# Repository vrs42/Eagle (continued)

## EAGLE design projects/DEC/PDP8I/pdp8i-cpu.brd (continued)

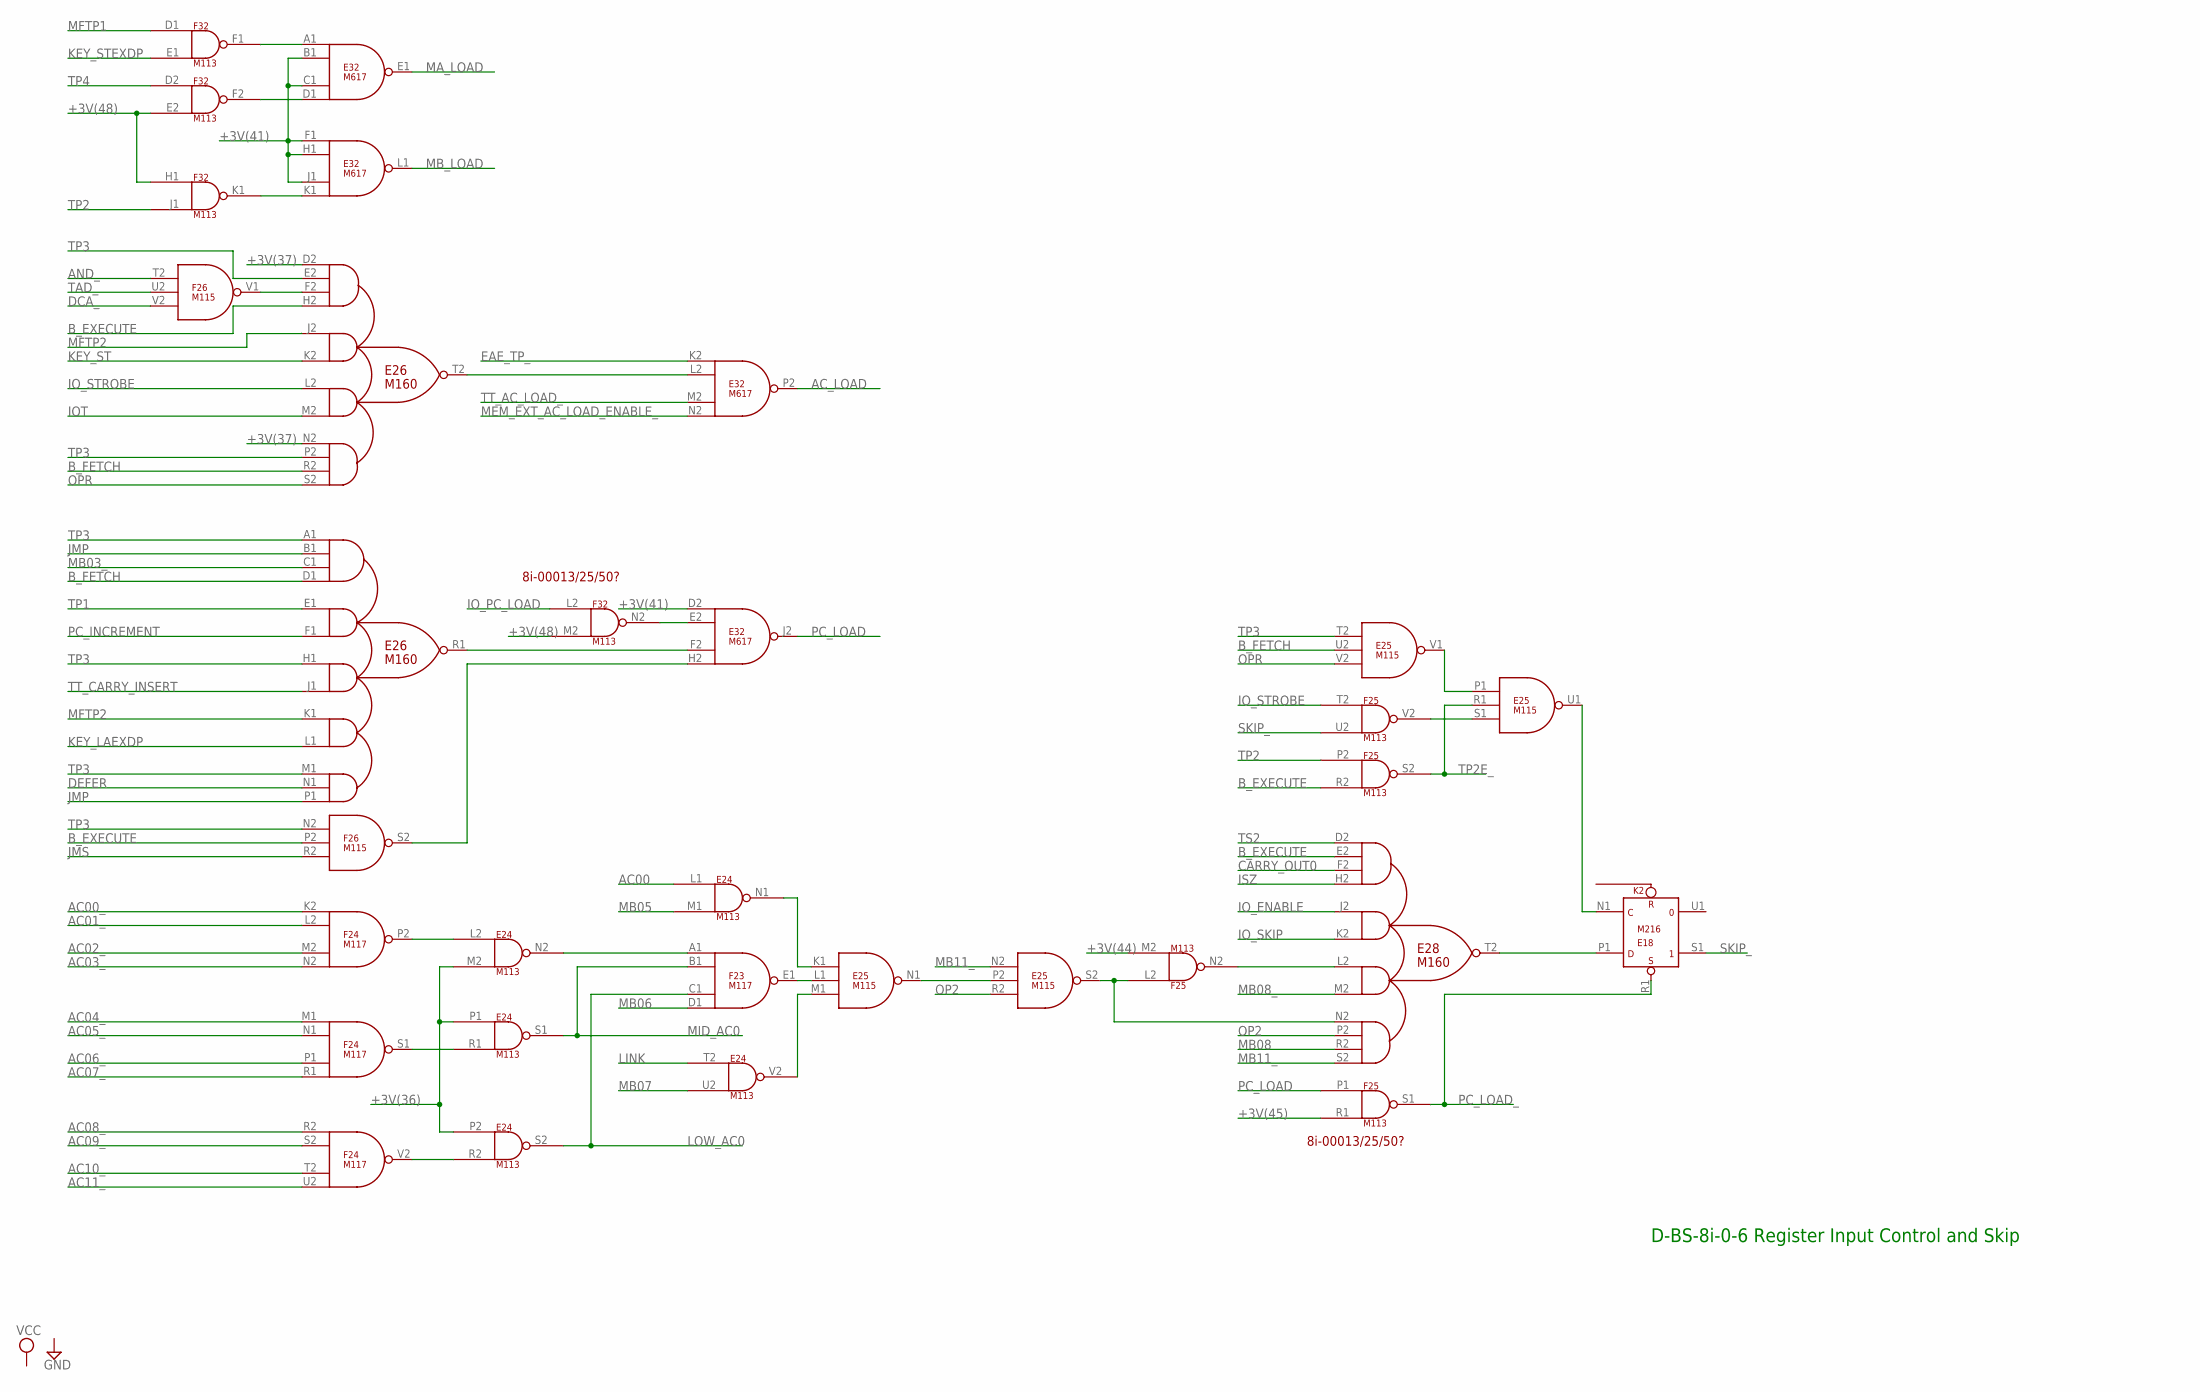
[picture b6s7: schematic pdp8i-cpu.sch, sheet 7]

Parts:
E18: M216; H807
E24: M113; H807
E25: M115; H807
E26, E28: M160; H807
E32: M617; H807
F23, F24: M117; H807
F25, F32: M113; H807
F26: M115; H807

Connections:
+3V(36): E24.M2 (IN2), E24.P1 (IN1), E24.P2 (IN1); also elsewhere on the board
+3V(37): E26.D2 (IN1A), E26.N2 (IN4A); also elsewhere on the board
+3V(41): E32.B1 (IN2), E32.C1 (IN3), E32.D2 (IN1), E32.F1 (IN1), E32.H1 (IN2), E32.J1 (IN3); also elsewhere on the board
+3V(44): F25.M2 (IN2); also elsewhere on the board
+3V(45): F25.R1 (IN2); also elsewhere on the board
+3V(48): F32.E2 (IN2), F32.H1 (IN1), F32.M2 (IN2); also elsewhere on the board
AC00: E24.L1 (IN1); also elsewhere on the board
AC00_: F24.K2 (IN1); also elsewhere on the board
AC01_: F24.L2 (IN2); also elsewhere on the board
AC02_: F24.M2 (IN3); also elsewhere on the board
AC03_: F24.N2 (IN4); also elsewhere on the board
AC04_: F24.M1 (IN1); also elsewhere on the board
AC05_: F24.N1 (IN2); also elsewhere on the board
AC06_: F24.P1 (IN3); also elsewhere on the board
AC07_: F24.R1 (IN4); also elsewhere on the board
AC08_: F24.R2 (IN1); also elsewhere on the board
AC09_: F24.S2 (IN2); also elsewhere on the board
AC10_: F24.T2 (IN3); also elsewhere on the board
AC11_: F24.U2 (IN4); also elsewhere on the board
AC_LOAD: E32.P2 (OUT); also elsewhere on the board
AND_: F26.T2 (IN1); also elsewhere on the board
B_EXECUTE: E26.H2 (IN1D), E28.E2 (IN1B), F25.R2 (IN2), F26.P2 (IN2); also elsewhere on the board
B_FETCH: E25.U2 (IN2), E26.D1 (IN1D), E26.R2 (IN4C); also elsewhere on the board
CARRY_OUT0: E28.F2 (IN1C); also elsewhere on the board
DCA_: F26.V2 (IN3); also elsewhere on the board
DEFER: E26.N1 (IN5B); also elsewhere on the board
EAE_TP_: E32.K2 (IN1); also elsewhere on the board
GND: E18.C2 (GND), E18.T1 (GND), E24.C2 (GND), E24.T1 (GND), E25.C2 (GND), E25.T1 (GND), E26.C2 (GND), E26.T1 (GND), E28.C2 (GND), E28.T1 (GND), E32.C2 (GND), E32.T1 (GND), F23.C2 (GND), F23.T1 (GND), F24.C2 (GND), F24.T1 (GND), F25.C2 (GND), F25.T1 (GND), F26.C2 (GND), F26.T1 (GND), F32.C2 (GND), F32.T1 (GND); also elsewhere on the board
IOT: E26.M2 (IN3B); also elsewhere on the board
IO_ENABLE: E28.J2 (IN2A); also elsewhere on the board
IO_PC_LOAD: F32.L2 (IN1); also elsewhere on the board
IO_SKIP: E28.K2 (IN2B); also elsewhere on the board
IO_STROBE: E26.L2 (IN3A), F25.T2 (IN1); also elsewhere on the board
ISZ: E28.H2 (IN1D); also elsewhere on the board
JMP: E26.B1 (IN1B), E26.P1 (IN5C); also elsewhere on the board
JMS: F26.R2 (IN3); also elsewhere on the board
KEY_LAEXDP: E26.L1 (IN4B); also elsewhere on the board
KEY_ST: E26.K2 (IN2B); also elsewhere on the board
KEY_STEXDP: F32.E1 (IN2); also elsewhere on the board
LINK: E24.T2 (IN1); also elsewhere on the board
LOW_AC0: E24.S2 (OUT), F23.C1 (IN3); also elsewhere on the board
MA_LOAD: E32.E1 (OUT); also elsewhere on the board
MB03_: E26.C1 (IN1C); also elsewhere on the board
MB05: E24.M1 (IN2); also elsewhere on the board
MB06: F23.D1 (IN4); also elsewhere on the board
MB07: E24.U2 (IN2); also elsewhere on the board
MB08: E28.R2 (IN4C); also elsewhere on the board
MB08_: E28.M2 (IN3B); also elsewhere on the board
MB11_: E25.N2 (IN1), E28.S2 (IN4D); also elsewhere on the board
MB_LOAD: E32.L1 (OUT); also elsewhere on the board
MEM_EXT_AC_LOAD_ENABLE_: E32.N2 (IN4); also elsewhere on the board
MFTP1: F32.D1 (IN1); also elsewhere on the board
MFTP2: E26.J2 (IN2A), E26.K1 (IN4A); also elsewhere on the board
MID_AC0: E24.S1 (OUT), F23.B1 (IN2); also elsewhere on the board
unnamed: E32.E2 (IN2), F32.N2 (OUT)
unnamed: E26.F2 (IN1C), F26.V1 (OUT)
unnamed: E26.T2 (OUT), E32.L2 (IN2)
unnamed: E26.R1 (OUT), E32.F2 (IN3)
unnamed: E32.H2 (IN4), F26.S2 (OUT)
unnamed: E24.R2 (IN2), F24.V2 (OUT)
unnamed: E24.R1 (IN2), F24.S1 (OUT)
unnamed: E24.L2 (IN1), F24.P2 (OUT)
unnamed: E25.L1 (IN2), F23.E1 (OUT)
unnamed: E24.V2 (OUT), E25.M1 (IN3)
unnamed: E24.N2 (OUT), F23.A1 (IN1)
unnamed: E24.N1 (OUT), E25.K1 (IN1)
unnamed: E25.N1 (OUT), E25.P2 (IN2)
unnamed: E28.L2 (IN3A), F25.N2 (OUT)
unnamed: E25.S2 (OUT), E28.N2 (IN4A), F25.L2 (IN1)
unnamed: E18.P1 (D), E28.T2 (OUT)
unnamed: E32.D1 (IN4), F32.F2 (OUT)
unnamed: E32.A1 (IN1), F32.F1 (OUT)
unnamed: E18.N1 (C), E25.U1 (OUT)
unnamed: E32.K1 (IN4), F32.K1 (OUT)
unnamed: E25.P1 (IN1), E25.V1 (OUT)
unnamed: E25.S1 (IN3), F25.V2 (OUT)
OP2: E25.R2 (IN3), E28.P2 (IN4B); also elsewhere on the board
OPR: E25.V2 (IN3), E26.S2 (IN4D); also elsewhere on the board
PC_INCREMENT: E26.F1 (IN2B); also elsewhere on the board
PC_LOAD: E32.J2 (OUT), F25.P1 (IN1); also elsewhere on the board
PC_LOAD_: E18.R1 (S), F25.S1 (OUT); also elsewhere on the board
SKIP_: E18.S1 (1), F25.U2 (IN2); also elsewhere on the board
TAD_: F26.U2 (IN2); also elsewhere on the board
TP1: E26.E1 (IN2A); also elsewhere on the board
TP2: F25.P2 (IN1), F32.J1 (IN2); also elsewhere on the board
TP2E_: E25.R1 (IN2), F25.S2 (OUT); also elsewhere on the board
TP3: E25.T2 (IN1), E26.A1 (IN1A), E26.E2 (IN1B), E26.H1 (IN3A), E26.M1 (IN5A), E26.P2 (IN4B), F26.N2 (IN1); also elsewhere on the board
TP4: F32.D2 (IN1); also elsewhere on the board
TS2: E28.D2 (IN1A); also elsewhere on the board
TT_AC_LOAD_: E32.M2 (IN3); also elsewhere on the board
TT_CARRY_INSERT: E26.J1 (IN3B); also elsewhere on the board
VCC: E18.A2 (VCC), E24.A2 (VCC), E25.A2 (VCC), E26.A2 (VCC), E28.A2 (VCC), E32.A2 (VCC), F23.A2 (VCC), F24.A2 (VCC), F25.A2 (VCC), F26.A2 (VCC), F32.A2 (VCC); also elsewhere on the board

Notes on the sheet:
D-BS-8i-0-6 Register Input Control and Skip
8i-00013/25/50?

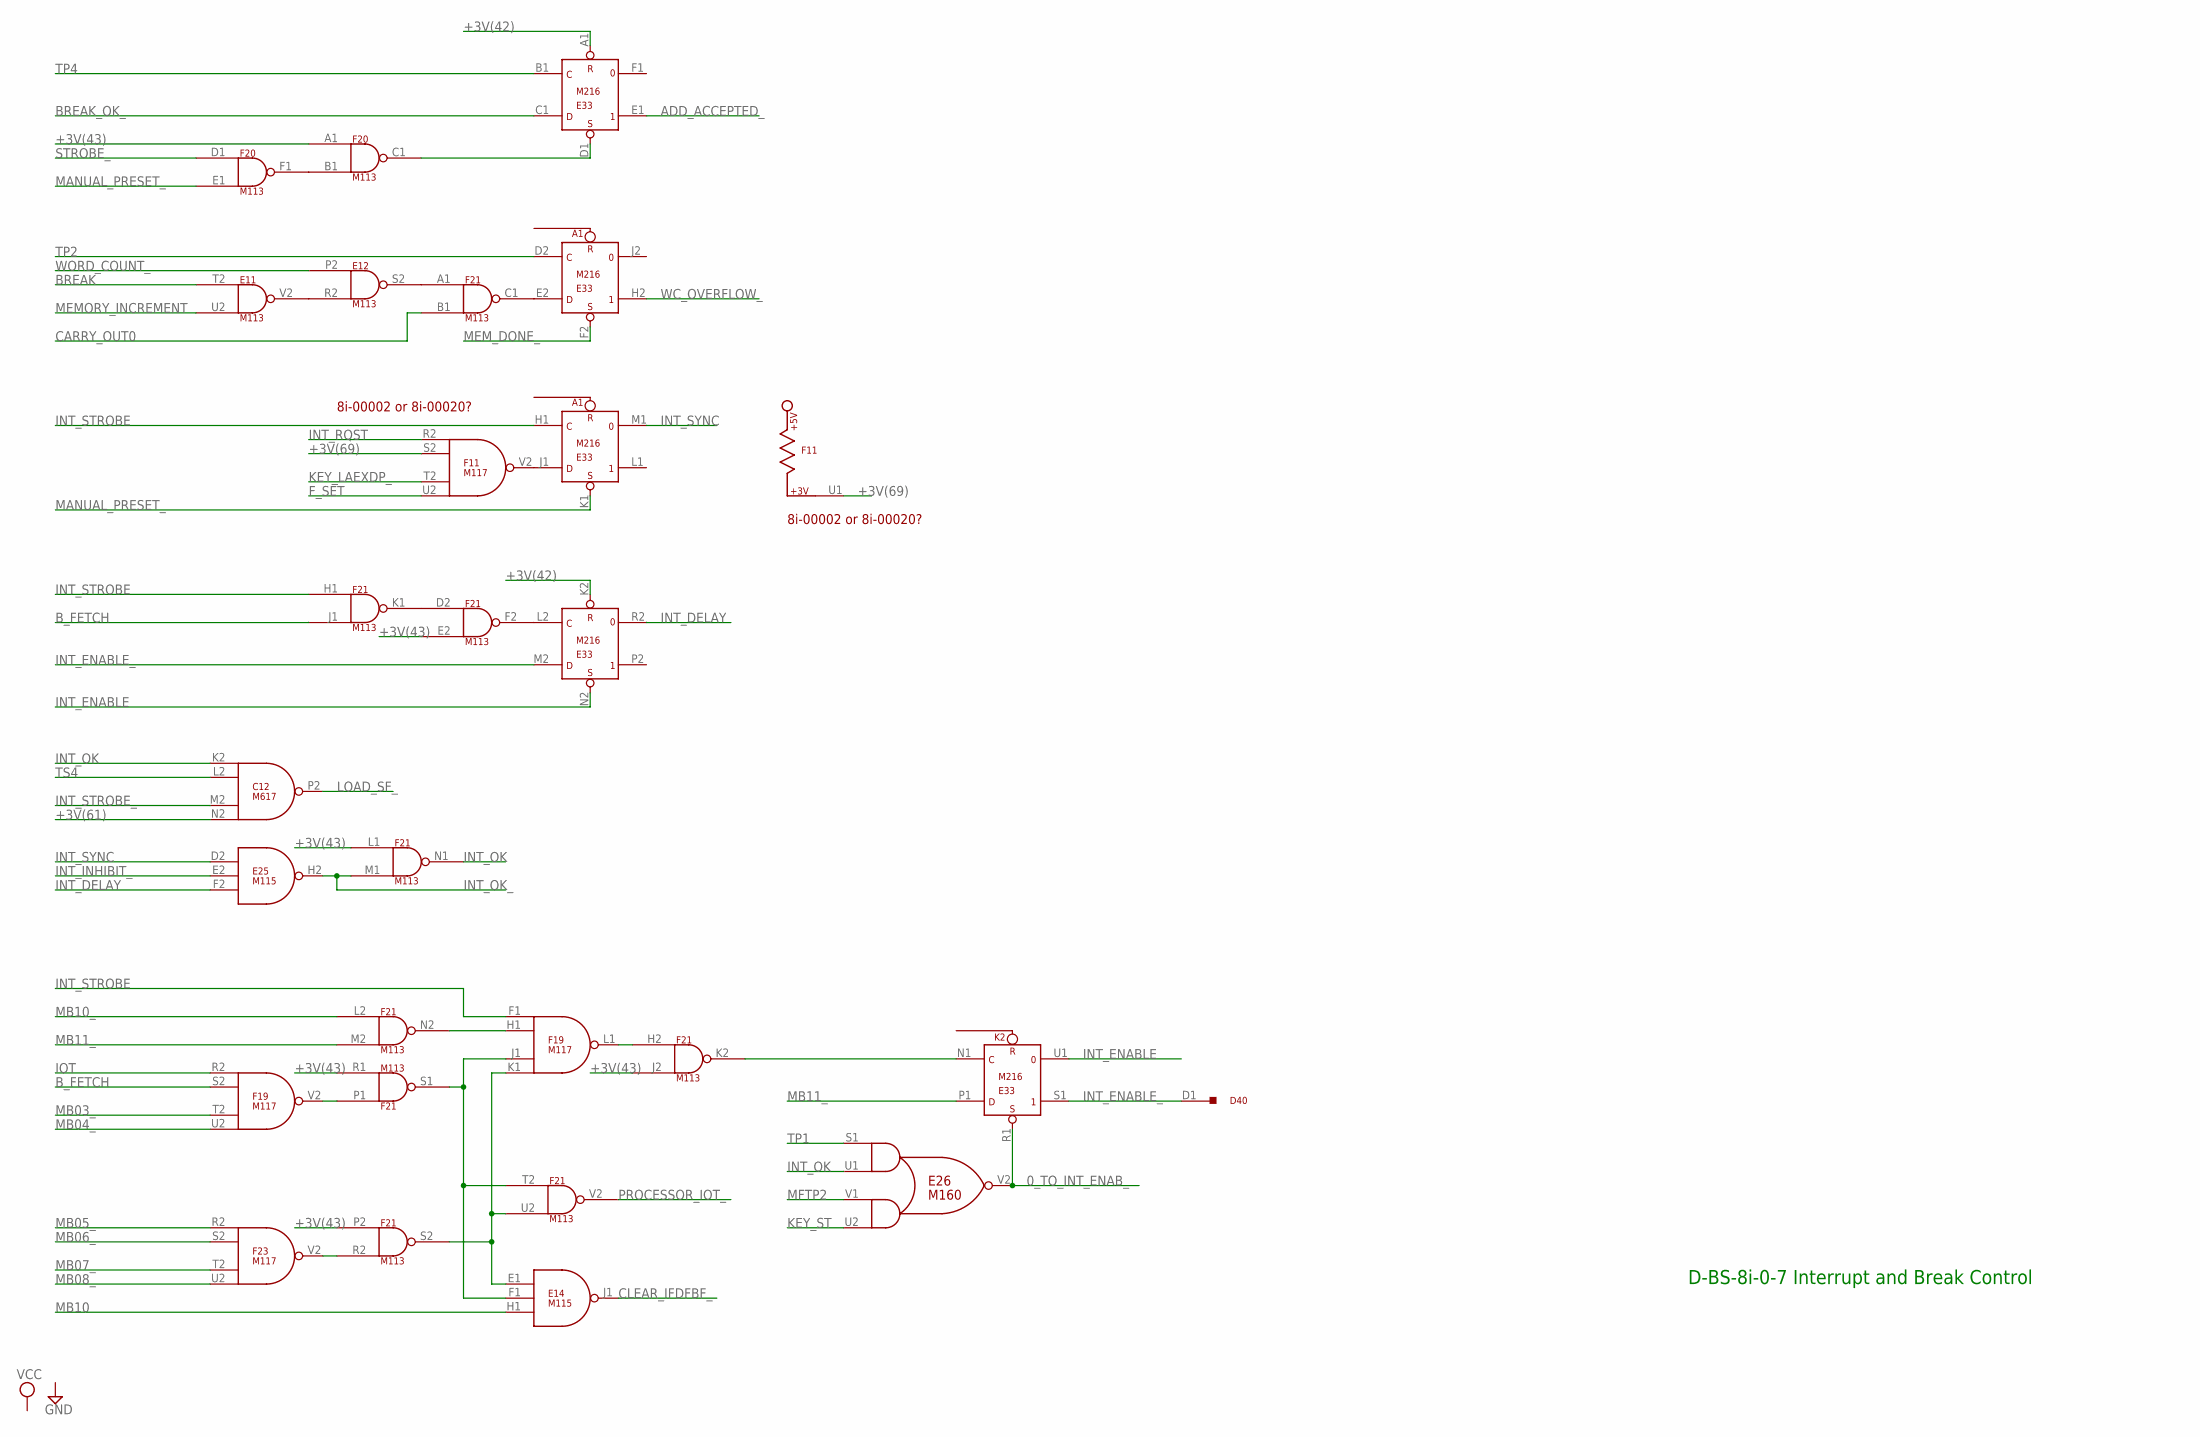
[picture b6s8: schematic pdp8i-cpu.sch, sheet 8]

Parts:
C12: M617; H807
D40: M900; H807
E11, E12: M113; H807
E14, E25: M115; H807
E26: M160; H807
E33: M216; H807
F11, F19, F23: M117; H807
F20, F21: M113; H807

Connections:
0_TO_INT_ENAB_: E26.V2 (OUT), E33.R1 (S)
+3V(42): E33.A1 (R), E33.K2 (R); also elsewhere on the board
+3V(43): F20.A1 (IN1), F21.E2 (IN2), F21.J2 (IN2), F21.L1 (IN1), F21.P2 (IN1), F21.R1 (IN2); also elsewhere on the board
+3V(61): C12.N2 (IN4); also elsewhere on the board
+3V(69): F11.S2 (IN2), F11.U1; also elsewhere on the board
ADD_ACCEPTED_: E33.E1 (1); also elsewhere on the board
BREAK: E11.T2 (IN1); also elsewhere on the board
BREAK_OK_: E33.C1 (D); also elsewhere on the board
B_FETCH: F19.S2 (IN2), F21.J1 (IN2); also elsewhere on the board
CARRY_OUT0: F21.B1 (IN2); also elsewhere on the board
CLEAR_IFDFBF_: E14.J1 (OUT); also elsewhere on the board
F_SET: F11.U2 (IN4); also elsewhere on the board
GND: C12.C2 (GND), C12.T1 (GND), E11.C2 (GND), E11.T1 (GND), E12.C2 (GND), E12.T1 (GND), E14.C2 (GND), E14.T1 (GND), E25.C2 (GND), E25.T1 (GND), E26.C2 (GND), E26.T1 (GND), E33.C2 (GND), E33.T1 (GND), F11.C2 (GND), F11.T1 (GND), F19.C2 (GND), F19.T1 (GND), F20.C2 (GND), F20.T1 (GND), F21.C2 (GND), F21.T1 (GND), F23.C2 (GND), F23.T1 (GND); also elsewhere on the board
INT_DELAY: E25.F2 (IN3), E33.R2 (0)
INT_ENABLE: E33.N2 (S), E33.U1 (0)
INT_ENABLE_: D40.D1, E33.M2 (D), E33.S1 (1)
INT_INHIBIT_: E25.E2 (IN2); also elsewhere on the board
INT_OK: C12.K2 (IN1), E26.U1 (IN1B), F21.N1 (OUT); also elsewhere on the board
INT_OK_: E25.H2 (OUT), F21.M1 (IN2); also elsewhere on the board
INT_RQST: F11.R2 (IN1); also elsewhere on the board
INT_STROBE: E33.H1 (C), F19.F1 (IN1), F21.H1 (IN1); also elsewhere on the board
INT_STROBE_: C12.M2 (IN3); also elsewhere on the board
INT_SYNC: E25.D2 (IN1), E33.M1 (0)
IOT: F19.R2 (IN1); also elsewhere on the board
KEY_LAEXDP_: F11.T2 (IN3); also elsewhere on the board
KEY_ST: E26.U2 (IN2B); also elsewhere on the board
LOAD_SF_: C12.P2 (OUT); also elsewhere on the board
MANUAL_PRESET_: E33.K1 (S), F20.E1 (IN2); also elsewhere on the board
MB03_: F19.T2 (IN3); also elsewhere on the board
MB04_: F19.U2 (IN4); also elsewhere on the board
MB05_: F23.R2 (IN1); also elsewhere on the board
MB06_: F23.S2 (IN2); also elsewhere on the board
MB07_: F23.T2 (IN3); also elsewhere on the board
MB08_: F23.U2 (IN4); also elsewhere on the board
MB10: E14.H1 (IN3); also elsewhere on the board
MB10_: F21.L2 (IN1); also elsewhere on the board
MB11_: E33.P1 (D), F21.M2 (IN2); also elsewhere on the board
MEMORY_INCREMENT: E11.U2 (IN2); also elsewhere on the board
MEM_DONE_: E33.F2 (S); also elsewhere on the board
MFTP2: E26.V1 (IN2A); also elsewhere on the board
unnamed: E33.J1 (D), F11.V2 (OUT)
unnamed: F20.B1 (IN2), F20.F1 (OUT)
unnamed: E33.D1 (S), F20.C1 (OUT)
unnamed: E11.V2 (OUT), E12.R2 (IN2)
unnamed: E12.S2 (OUT), F21.A1 (IN1)
unnamed: E33.E2 (D), F21.C1 (OUT)
unnamed: F21.D2 (IN1), F21.K1 (OUT)
unnamed: E33.L2 (C), F21.F2 (OUT)
unnamed: E33.N1 (C), F21.K2 (OUT)
unnamed: F19.H1 (IN2), F21.N2 (OUT)
unnamed: E14.F1 (IN2), F19.J1 (IN3), F21.S1 (OUT), F21.T2 (IN1)
unnamed: F19.V2 (OUT), F21.P1 (IN1)
unnamed: F19.L1 (OUT), F21.H2 (IN1)
unnamed: F21.R2 (IN2), F23.V2 (OUT)
unnamed: E14.E1 (IN1), F19.K1 (IN4), F21.S2 (OUT), F21.U2 (IN2)
PROCESSOR_IOT_: F21.V2 (OUT); also elsewhere on the board
STROBE_: F20.D1 (IN1); also elsewhere on the board
TP1: E26.S1 (IN1A); also elsewhere on the board
TP2: E33.D2 (C); also elsewhere on the board
TP4: E33.B1 (C); also elsewhere on the board
TS4: C12.L2 (IN2); also elsewhere on the board
VCC: C12.A2 (VCC), E11.A2 (VCC), E12.A2 (VCC), E14.A2 (VCC), E25.A2 (VCC), E26.A2 (VCC), E33.A2 (VCC), F11.A2 (VCC), F19.A2 (VCC), F20.A2 (VCC), F21.A2 (VCC), F23.A2 (VCC); also elsewhere on the board
WC_OVERFLOW_: E33.H2 (1); also elsewhere on the board
WORD_COUNT_: E12.P2 (IN1); also elsewhere on the board

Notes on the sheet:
D-BS-8i-0-7 Interrupt and Break Control
8i-00002 or 8i-00020?

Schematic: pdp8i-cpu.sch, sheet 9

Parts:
C40: M900; H807
E33: M216; H807
E40: M900; H807
EF34, EF35, EF36, EF37, EF38, EF39: M220; H807-2
F28: M115; H807
F32: M113; H807
F33: M160; H807
F40: M900; H807

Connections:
+3V(42): E33.U2 (S); also elsewhere on the board
+3V(48): F32.P2 (IN1), F32.R1 (IN2), F32.T2 (IN1), F33.C1 (IN1C), F33.D2 (IN1A), F33.P1 (IN5C); also elsewhere on the board
AC00: EF34.BA1, F33.N2 (IN4A); also elsewhere on the board
AC00_: E40.V2, EF34.BB1; also elsewhere on the board
AC01: EF34.AV1; also elsewhere on the board
AC01_: E40.T2, EF34.AV2; also elsewhere on the board
AC02: EF35.BA1; also elsewhere on the board
AC02_: E40.J1, EF35.BB1; also elsewhere on the board
AC03: EF35.AV1; also elsewhere on the board
AC03_: E40.H2, EF35.AV2; also elsewhere on the board
AC04: EF36.BA1; also elsewhere on the board
AC04_: E40.M1, EF36.BB1; also elsewhere on the board
AC05: EF36.AV1; also elsewhere on the board
AC05_: E40.B1, EF36.AV2; also elsewhere on the board
AC06: EF37.BA1; also elsewhere on the board
AC06_: EF37.BB1, F40.V2; also elsewhere on the board
AC07: EF37.AV1; also elsewhere on the board
AC07_: EF37.AV2, F40.T2; also elsewhere on the board
AC08: EF38.BA1; also elsewhere on the board
AC08_: EF38.BB1, F40.J1; also elsewhere on the board
AC09: EF38.AV1; also elsewhere on the board
AC09_: EF38.AV2, F40.H2; also elsewhere on the board
AC10: EF39.BA1; also elsewhere on the board
AC10_: EF39.BB1, F40.M1; also elsewhere on the board
AC11: EF39.AV1; also elsewhere on the board
AC11_: EF39.AV2, F40.B1; also elsewhere on the board
AC_LOAD: E33.S2 (C), EF34.AU1, EF35.AU1, EF36.AU1, EF37.AU1, EF38.AU1, EF39.AU1; also elsewhere on the board
ADDER00: F33.K1 (IN4A); also elsewhere on the board
ADDER01: F33.M1 (IN5A); also elsewhere on the board
ADDER10: F33.E1 (IN2A); also elsewhere on the board
ADDER11: F32.P1 (IN1); also elsewhere on the board
ADDER11_: F28.P1 (IN1), F32.S1 (OUT); also elsewhere on the board
ADDER_L_: F33.H1 (IN3A), F33.V2 (OUT); also elsewhere on the board
ASR_ENABLE: F33.R2 (IN4C); also elsewhere on the board
ASR_L_SET_: F33.B1 (IN1B); also elsewhere on the board
B_EAE_ON: F33.P2 (IN4B); also elsewhere on the board
CARRY_OUT0: F32.V2 (OUT), F33.U1 (IN1B); also elsewhere on the board
CARRY_OUT0_: F32.U2 (IN2), F33.U2 (IN2B); also elsewhere on the board
DOUBLE_LEFT_ROTATE: F33.N1 (IN5B); also elsewhere on the board
DOUBLE_RIGHT_ROTATE: F33.F1 (IN2B); also elsewhere on the board
EAE_IR2_: F33.S2 (IN4D); also elsewhere on the board
EAE_ON_: F28.R1 (IN2); also elsewhere on the board
GND: C40.C2, E33.C2 (GND), E33.T1 (GND), E40.C2, EF34.AC2 (GND), EF34.AT1 (GND), EF34.BC2 (GND), EF34.BT1 (GND), EF35.AC2 (GND), EF35.AT1 (GND), EF35.BC2 (GND), EF35.BT1 (GND), EF36.AC2 (GND), EF36.AT1 (GND), EF36.BC2 (GND), EF36.BT1 (GND), EF37.AC2 (GND), EF37.AT1 (GND), EF37.BC2 (GND), EF37.BT1 (GND), EF38.AC2 (GND), EF38.AT1 (GND), EF38.BC2 (GND), EF38.BT1 (GND), EF39.AC2 (GND), EF39.AT1 (GND), EF39.BC2 (GND), EF39.BT1 (GND), F28.C2 (GND), F28.T1 (GND), F32.C2 (GND), F32.T1 (GND), F33.C2 (GND), F33.T1 (GND), F40.C2; also elsewhere on the board
LBAR_ENABLE: F33.M2 (IN3B); also elsewhere on the board
LEFT_SHIFT: F33.L1 (IN4B); also elsewhere on the board
LINK: E33.V2 (1), F33.J2 (IN2A); also elsewhere on the board
LINK_: C40.B1, E33.V1 (0), F33.L2 (IN3A)
L_ENABLE: F33.K2 (IN2B); also elsewhere on the board
MA00_: E40.U2, EF34.AM1; also elsewhere on the board
MA01_: E40.R2, EF34.AL1; also elsewhere on the board
MA02_: E40.K2, EF35.AM1; also elsewhere on the board
MA03_: E40.E2, EF35.AL1; also elsewhere on the board
MA04_: E40.L1, EF36.AM1; also elsewhere on the board
MA05_: E40.E1, EF36.AL1; also elsewhere on the board
MA06_: EF37.AM1, F40.U2; also elsewhere on the board
MA07_: EF37.AL1, F40.R2; also elsewhere on the board
MA08: EF38.AM2; also elsewhere on the board
MA08_: EF38.AM1, F40.K2; also elsewhere on the board
MA09_: EF38.AL1, F40.E2; also elsewhere on the board
MA10_: EF39.AM1, F40.L1; also elsewhere on the board
MA11_: EF39.AL1, F40.E1; also elsewhere on the board
MA_LOAD: EF34.AK1, EF35.AK1, EF36.AK1, EF37.AK1, EF38.AK1, EF39.AK1; also elsewhere on the board
MB00: EF34.AT2; also elsewhere on the board
MB00_: E40.R1, EF34.AU2; also elsewhere on the board
MB01: EF34.AS2; also elsewhere on the board
MB01_: E40.P1, EF34.AS1; also elsewhere on the board
MB02: EF35.AT2; also elsewhere on the board
MB02_: E40.F2, EF35.AU2; also elsewhere on the board
MB03: EF35.AS2; also elsewhere on the board
MB03_: E40.D2, EF35.AS1; also elsewhere on the board
MB04: EF36.AT2; also elsewhere on the board
MB04_: E40.K1, EF36.AU2; also elsewhere on the board
MB05: EF36.AS2; also elsewhere on the board
MB05_: E40.A1, EF36.AS1; also elsewhere on the board
MB06: EF37.AT2; also elsewhere on the board
MB06_: EF37.AU2, F40.R1; also elsewhere on the board
MB07: EF37.AS2; also elsewhere on the board
MB07_: EF37.AS1, F40.P1; also elsewhere on the board
MB08: EF38.AT2; also elsewhere on the board
MB08_: EF38.AU2, F40.F2; also elsewhere on the board
MB09: EF38.AS2; also elsewhere on the board
MB09_: EF38.AS1, F40.D2; also elsewhere on the board
MB10: EF39.AT2; also elsewhere on the board
MB10_: EF39.AU2, F40.K1; also elsewhere on the board
MB11: EF39.AS2; also elsewhere on the board
MB11_: EF39.AS1, F40.A1; also elsewhere on the board
MB_LOAD: EF34.AR1, EF35.AR1, EF36.AR1, EF37.AR1, EF38.AR1, EF39.AR1; also elsewhere on the board
unnamed: E33.T2 (D), F33.R1 (OUT)
unnamed: F32.S2 (OUT), F33.V1 (IN2A)
unnamed: F28.U1 (OUT), F33.A1 (IN1A)
unnamed: F32.R2 (IN2), F33.S1 (IN1A), F33.T2 (OUT)
NO_SHIFT: F33.J1 (IN3B); also elsewhere on the board
PC00_: E40.J2, EF34.AR2
PC01_: E40.S1, EF34.AP2
PC02_: E40.P2, EF35.AR2
PC03_: E40.N1, EF35.AP2
PC04_: E40.C1, EF36.AR2
PC05_: E40.D1, EF36.AP2
PC06_: EF37.AR2, F40.J2
PC07_: EF37.AP2, F40.S1
PC08_: EF38.AR2, F40.P2
PC09_: EF38.AP2, F40.N1
PC10_: EF39.AR2, F40.C1
PC11_: EF39.AP2, F40.D1
PC_LOAD: EF34.AN2, EF35.AN2, EF36.AN2, EF37.AN2, EF38.AN2, EF39.AN2; also elsewhere on the board
RIGHT_SHIFT: F33.D1 (IN1D); also elsewhere on the board
TT_DATA: F33.H2 (IN1D); also elsewhere on the board
TT_INST_: F28.S1 (IN3), F33.F2 (IN1C); also elsewhere on the board
TT_SHIFT_ENABLE: F33.E2 (IN1B); also elsewhere on the board
VCC: C40.A2, E33.A2 (VCC), E40.A2, EF34.AA2 (VCC), EF34.BA2 (VCC), EF35.AA2 (VCC), EF35.BA2 (VCC), EF36.AA2 (VCC), EF36.BA2 (VCC), EF37.AA2 (VCC), EF37.BA2 (VCC), EF38.AA2 (VCC), EF38.BA2 (VCC), EF39.AA2 (VCC), EF39.BA2 (VCC), F28.A2 (VCC), F32.A2 (VCC), F33.A2 (VCC), F40.A2; also elsewhere on the board

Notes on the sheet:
D-BS-8i-0-8 Major Registers
REG_BUS00
REG_BUS01
REG_BUS02
REG_BUS03
REG_BUS04
REG_BUS05
REG_BUS06
REG_BUS07
REG_BUS08
REG_BUS09
REG_BUS10
REG_BUS11

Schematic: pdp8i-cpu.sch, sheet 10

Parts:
A40: W077; H807
EF34, EF35: M220; H807-2

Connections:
ACBAR_ENABLE: EF34.BJ2, EF35.BJ2; also elsewhere on the board
AC_ENABLE: EF34.BH2, EF35.BH2; also elsewhere on the board
ADDER00: EF34.AE2, EF35.AB1; also elsewhere on the board
ADDER01: EF34.AF1, EF35.AC1; also elsewhere on the board
ADDER02: EF34.AH2, EF35.AE2, EF35.BB2; also elsewhere on the board
ADDER03: EF34.AJ2, EF35.AF1; also elsewhere on the board
ADDER04: EF35.AH2; also elsewhere on the board
ADDER05: EF35.AJ2; also elsewhere on the board
ADDER11: EF34.AB1; also elsewhere on the board
ADDER_L_: EF34.AC1, EF34.BB2; also elsewhere on the board
AND_ENABLE: EF34.AA1, EF35.AA1; also elsewhere on the board
CARRY_OUT0_: EF34.BK2; also elsewhere on the board
DATA00: EF34.BM2; also elsewhere on the board
DATA01: EF34.BP2; also elsewhere on the board
DATA02: EF35.BM2; also elsewhere on the board
DATA_ADD00: EF34.BS1; also elsewhere on the board
DATA_ADD01: EF34.BU1; also elsewhere on the board
DATA_ADD02: EF35.BS1; also elsewhere on the board
DATA_ADD_ENABLE: EF34.BT2, EF35.BT2; also elsewhere on the board
DATA_ENABLE: EF34.BL1, EF35.BL1; also elsewhere on the board
DOUBLE_LEFT_ROTATE: EF34.AH1, EF35.AH1; also elsewhere on the board
DOUBLE_RIGHT_ROTATE: EF34.AD1, EF35.AD1; also elsewhere on the board
GND: EF34.AC2 (GND), EF34.AT1 (GND), EF34.BC2 (GND), EF34.BD1, EF34.BE2, EF34.BN1, EF34.BT1 (GND), EF35.AC2 (GND), EF35.AT1 (GND), EF35.BC2 (GND), EF35.BD1, EF35.BT1 (GND); also elsewhere on the board
INPUT_BUS00: EF34.BK1; also elsewhere on the board
INPUT_BUS01: EF34.BM1; also elsewhere on the board
INPUT_BUS02: EF35.BK1; also elsewhere on the board
IO_ENABLE: EF34.BL2, EF35.BL2; also elsewhere on the board
LEFT_SHIFT: EF34.AF2, EF35.AF2; also elsewhere on the board
MA_ENABLE0_4: EF34.BP1, EF34.BR2, EF35.BP1; also elsewhere on the board
MEM00: EF34.BR1; also elsewhere on the board
MEM01: EF34.BV2; also elsewhere on the board
MEM02: EF35.BR1; also elsewhere on the board
MEM_ENABLE0_4: EF34.BU2, EF34.BV1, EF35.BU2; also elsewhere on the board
MQ00: EF34.BH1; also elsewhere on the board
MQ01: EF34.BN2; also elsewhere on the board
MQ02: EF35.BH1; also elsewhere on the board
MQ_ENABLE: EF34.BF1, EF35.BF1; also elsewhere on the board
unnamed: EF34.BJ1, EF35.BK2
NO_SHIFT: EF34.AE1, EF35.AE1; also elsewhere on the board
PC_ENABLE: EF34.BS2, EF35.BS2; also elsewhere on the board
RIGHT_SHIFT: EF34.AD2, EF35.AD2; also elsewhere on the board
SC_ENABLE: EF34.BF2, EF35.BF2; also elsewhere on the board
SR00: A40.L2, EF34.BE1
SR01: A40.M2, EF34.BD2
SR02: A40.R2, EF35.BE1
SR_ENABLE: EF34.BC1, EF35.BC1; also elsewhere on the board
TT_LINE_SHIFT_: EF34.AB2, EF35.AB2; also elsewhere on the board
VCC: EF34.AA2 (VCC), EF34.BA2 (VCC), EF35.AA2 (VCC), EF35.BA2 (VCC); also elsewhere on the board

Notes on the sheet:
D-BS-8i-0-9 Major Registers Gating (1/4)
REG_BUS00
REG_BUS01
REG_BUS02
CARRY_OUT3_

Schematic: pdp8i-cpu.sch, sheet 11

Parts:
A40: W077; H807
EF35, EF36: M220; H807-2

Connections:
ACBAR_ENABLE: EF36.BJ2; also elsewhere on the board
AC_ENABLE: EF36.BH2; also elsewhere on the board
ADDER02: EF36.AB1; also elsewhere on the board
ADDER03: EF36.AC1; also elsewhere on the board
ADDER04: EF36.AE2, EF36.BB2; also elsewhere on the board
ADDER05: EF36.AF1; also elsewhere on the board
ADDER06: EF36.AH2; also elsewhere on the board
ADDER07: EF36.AJ2; also elsewhere on the board
AND_ENABLE: EF36.AA1; also elsewhere on the board
CARRY_OUT6_: EF36.BJ1; also elsewhere on the board
DATA03: EF35.BP2; also elsewhere on the board
DATA04: EF36.BM2; also elsewhere on the board
DATA05: EF36.BP2; also elsewhere on the board
DATA_ADD03: EF35.BU1; also elsewhere on the board
DATA_ADD04: EF36.BS1; also elsewhere on the board
DATA_ADD05: EF36.BU1; also elsewhere on the board
DATA_ADD_ENABLE: EF36.BT2; also elsewhere on the board
DATA_ENABLE: EF36.BL1; also elsewhere on the board
DOUBLE_LEFT_ROTATE: EF36.AH1; also elsewhere on the board
DOUBLE_RIGHT_ROTATE: EF36.AD1; also elsewhere on the board
GND: EF35.AC2 (GND), EF35.AT1 (GND), EF35.BC2 (GND), EF35.BE2, EF35.BN1, EF35.BT1 (GND), EF36.AC2 (GND), EF36.AT1 (GND), EF36.BC2 (GND), EF36.BD1, EF36.BE2, EF36.BN1, EF36.BT1 (GND); also elsewhere on the board
INPUT_BUS03: EF35.BM1; also elsewhere on the board
INPUT_BUS04: EF36.BK1; also elsewhere on the board
INPUT_BUS05: EF36.BM1; also elsewhere on the board
IO_ENABLE: EF36.BL2; also elsewhere on the board
LEFT_SHIFT: EF36.AF2; also elsewhere on the board
MA_ENABLE0_4: EF35.BR2, EF36.BP1; also elsewhere on the board
MA_ENABLE5_11: EF36.BR2; also elsewhere on the board
MEM03: EF35.BV2; also elsewhere on the board
MEM04: EF36.BR1; also elsewhere on the board
MEM05: EF36.BV2; also elsewhere on the board
MEM_ENABLE0_4: EF35.BV1, EF36.BU2; also elsewhere on the board
MEM_ENABLE5_8: EF36.BV1; also elsewhere on the board
MQ03: EF35.BN2; also elsewhere on the board
MQ04: EF36.BH1; also elsewhere on the board
MQ05: EF36.BN2; also elsewhere on the board
MQ_ENABLE: EF36.BF1; also elsewhere on the board
unnamed: EF35.BJ1, EF36.BK2
NO_SHIFT: EF36.AE1; also elsewhere on the board
PC_ENABLE: EF36.BS2; also elsewhere on the board
RIGHT_SHIFT: EF36.AD2; also elsewhere on the board
SC_ENABLE: EF36.BF2; also elsewhere on the board
SR03: A40.S2, EF35.BD2
SR04: A40.T2, EF36.BE1
SR05: A40.U2, EF36.BD2
SR_ENABLE: EF36.BC1; also elsewhere on the board
TT_LINE_SHIFT_: EF36.AB2; also elsewhere on the board
VCC: EF35.AA2 (VCC), EF35.BA2 (VCC), EF36.AA2 (VCC), EF36.BA2 (VCC); also elsewhere on the board

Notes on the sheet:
D-BS-8i-0-9 Major Registers Gating (2/4)
REG_BUS03
REG_BUS04
REG_BUS05

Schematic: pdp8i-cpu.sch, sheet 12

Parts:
A40: W077; H807
B40: W077; H807
EF37, EF38: M220; H807-2

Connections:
ACBAR_ENABLE: EF37.BJ2, EF38.BJ2; also elsewhere on the board
AC_ENABLE: EF37.BH2, EF38.BH2; also elsewhere on the board
ADDER04: EF37.AB1; also elsewhere on the board
ADDER05: EF37.AC1; also elsewhere on the board
ADDER06: EF37.AE2, EF37.BB2, EF38.AB1; also elsewhere on the board
ADDER07: EF37.AF1, EF38.AC1; also elsewhere on the board
ADDER08: EF37.AH2, EF38.AE2, EF38.BB2; also elsewhere on the board
ADDER09: EF37.AJ2, EF38.AF1; also elsewhere on the board
ADDER10: EF38.AH2; also elsewhere on the board
ADDER11: EF38.AJ2; also elsewhere on the board
AND_ENABLE: EF37.AA1, EF38.AA1; also elsewhere on the board
CARRY_OUT6_: EF37.BK2; also elsewhere on the board
DATA06: EF37.BM2; also elsewhere on the board
DATA07: EF37.BP2; also elsewhere on the board
DATA08: EF38.BM2; also elsewhere on the board
DATA_ADD06: EF37.BS1; also elsewhere on the board
DATA_ADD07: EF37.BU1; also elsewhere on the board
DATA_ADD08: EF38.BS1; also elsewhere on the board
DATA_ADD_ENABLE: EF37.BT2, EF38.BT2; also elsewhere on the board
DATA_ENABLE: EF37.BL1, EF38.BL1; also elsewhere on the board
DOUBLE_LEFT_ROTATE: EF37.AH1, EF38.AH1; also elsewhere on the board
DOUBLE_RIGHT_ROTATE: EF37.AD1, EF38.AD1; also elsewhere on the board
GND: A40.C2, B40.C2, EF37.AC2 (GND), EF37.AT1 (GND), EF37.BC2 (GND), EF37.BD1, EF37.BE2, EF37.BT1 (GND), EF38.AC2 (GND), EF38.AT1 (GND), EF38.BC2 (GND), EF38.BT1 (GND); also elsewhere on the board
INPUT_BUS06: EF37.BK1; also elsewhere on the board
INPUT_BUS07: EF37.BM1; also elsewhere on the board
INPUT_BUS08: EF38.BK1; also elsewhere on the board
IO_ENABLE: EF37.BL2, EF38.BL2; also elsewhere on the board
LEFT_SHIFT: EF37.AF2, EF38.AF2; also elsewhere on the board
MA_ENABLE5_11: EF37.BP1, EF37.BR2, EF38.BP1; also elsewhere on the board
MEM06: EF37.BR1; also elsewhere on the board
MEM07: EF37.BV2; also elsewhere on the board
MEM08: EF38.BR1; also elsewhere on the board
MEM_ENABLE5_8: EF37.BU2, EF37.BV1, EF38.BU2; also elsewhere on the board
MQ06: EF37.BH1; also elsewhere on the board
MQ07: EF37.BN2; also elsewhere on the board
MQ08: EF38.BH1; also elsewhere on the board
MQ_ENABLE: EF37.BF1, EF38.BF1; also elsewhere on the board
unnamed: EF37.BJ1, EF38.BK2
NO_SHIFT: EF37.AE1, EF38.AE1; also elsewhere on the board
PC_ENABLE: EF37.BS2, EF38.BS2; also elsewhere on the board
RIGHT_SHIFT: EF37.AD2, EF38.AD2; also elsewhere on the board
SC0: EF37.BN1; also elsewhere on the board
SC1: EF38.BD1; also elsewhere on the board
SC_ENABLE: EF37.BF2, EF38.BF2; also elsewhere on the board
SR06: A40.V2, EF37.BE1
SR07: B40.D2, EF37.BD2
SR08: B40.E2, EF38.BE1
SR_ENABLE: EF37.BC1, EF38.BC1; also elsewhere on the board
TT_LINE_SHIFT_: EF37.AB2, EF38.AB2; also elsewhere on the board
VCC: A40.A2, B40.A2, EF37.AA2 (VCC), EF37.BA2 (VCC), EF38.AA2 (VCC), EF38.BA2 (VCC); also elsewhere on the board

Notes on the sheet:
D-BS-8i-0-9 Major Registers Gating (3/4)
REG_BUS06
REG_BUS07
REG_BUS08
CARRY_OUT9_
